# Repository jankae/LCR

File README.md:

# LCR Meter

### Key specifications
* Measurement frequency: 100Hz-200kHz
* Usable impedance range: 20mOhm-1MOhm (measurements above and below this range are possible but due to very low ADC values, the reported phase will be quite noisy)
### Some useful features
* Optionally apply DC bias voltage up to 10V (measure effective capacitance of MLCCs)
* Autoranging
* Open/Short calibration (lead compensation)
* Fully configurable sweep, showing up to two parameters across frequency:
  * Impedance
  * Phase
  * Capacitance
  * Inductance
  * ESR
  * Quality factor
##### Example of a sweep, showing the self-resonant frequency of a capacitor at approximately 5.5kHz

#### Modified version:
* Two possible toolchains: System Workbench for STM32 or IAR
* Slightly modified PCB
* Laser-cut acrylic case
##### Resistance measurement 1 kOhm +- 0.1%

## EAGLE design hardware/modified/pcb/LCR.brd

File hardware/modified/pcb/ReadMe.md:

Changed electrical circuit and printed circuit board:
- TAG-CONNECT ICSP connector replaced with pin header
- SI8651EB-B-IU replaced by ADuM1401CRWZ
- added USBLC6-2P6 for ESD protection on USB
- the display pin header is moved closer to the edge of the board for a display tighter fit
- added a fourth hole for mounting

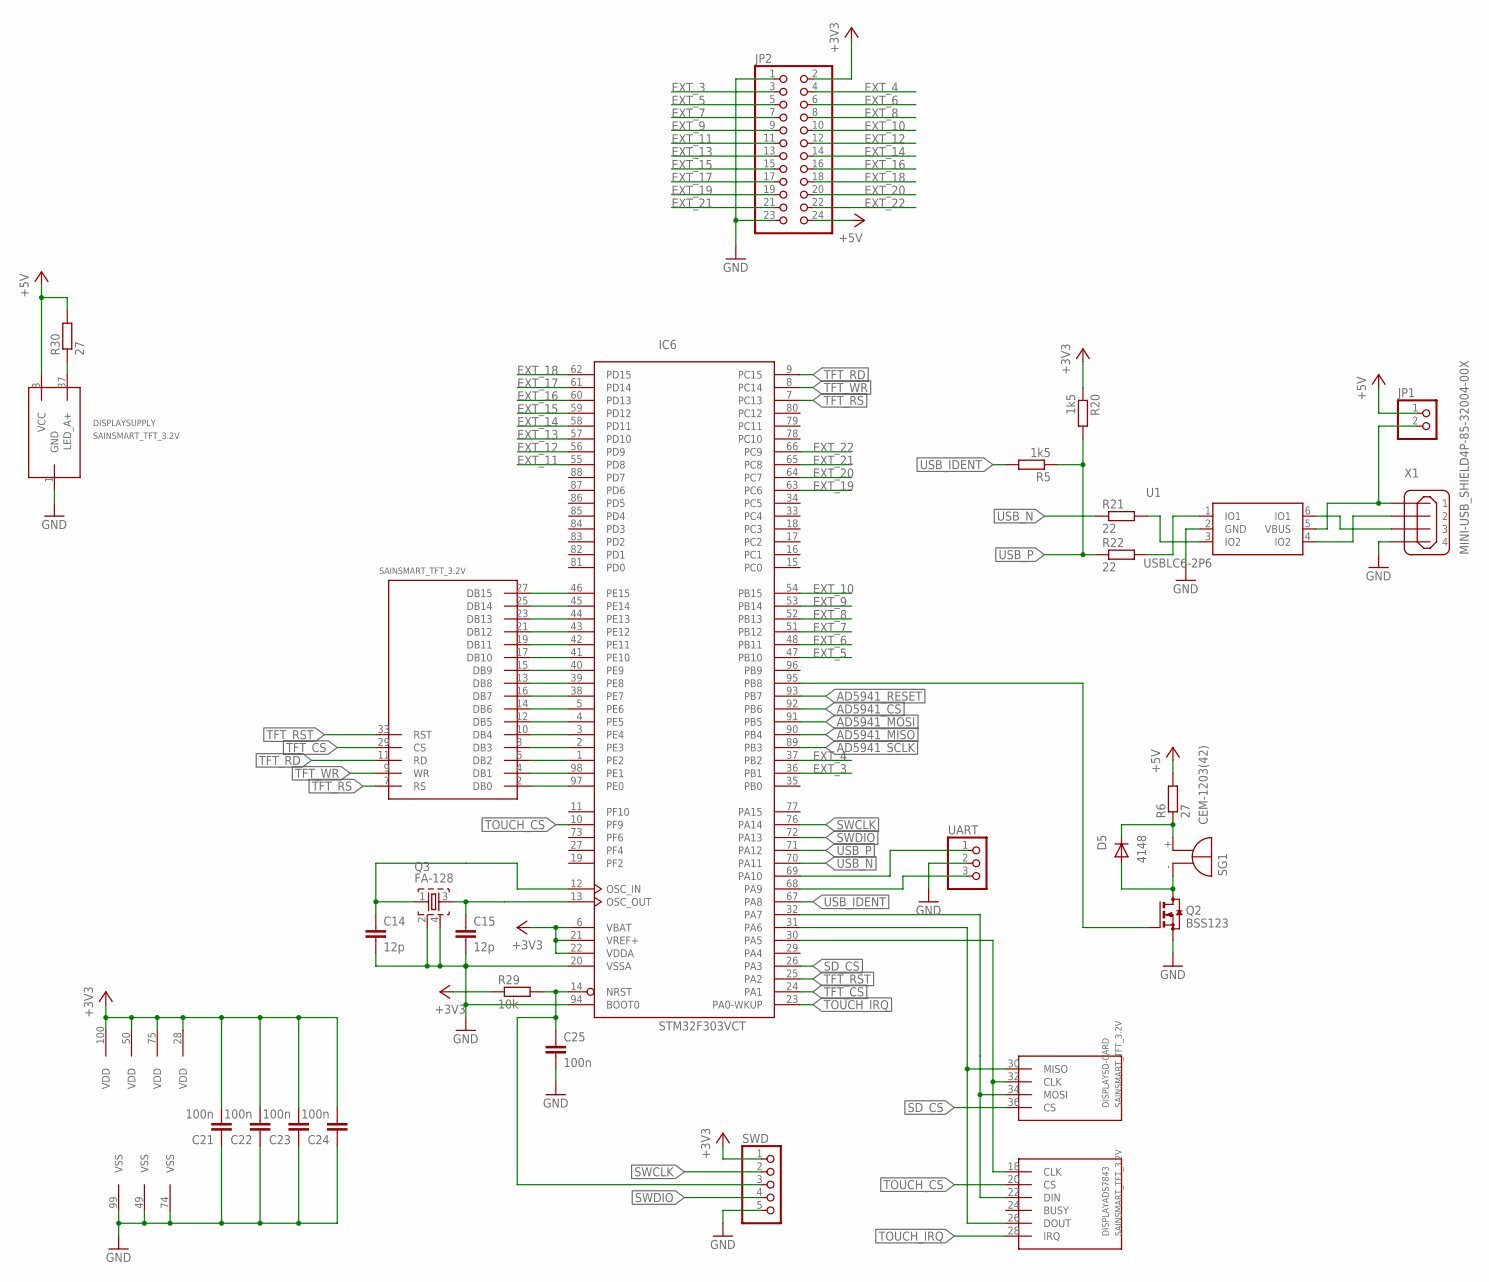
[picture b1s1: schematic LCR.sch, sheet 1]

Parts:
C14, C15: 12p; C0603K
C21, C22, C23, C24, C25: 100n; C0603K
D5: 4148; SOD123
DISPLAY: SAINSMART_TFT_3.2V; SAINSMART_ANGLED
IC6: STM32F303VCT; LQFP100
JP1: PINHD-1X2; 1X02
JP2: PINHD-2X12; 2X12
Q2: BSS123; SOT23
Q3: FA-128
R5, R20: 1k5; R0603
R6, R30: 27; R1206
R21, R22: 22; R0603
R29: 10k; R0603
SG1: CEM-1203(42); F/QMBIII
SWD: PINHD-1X5; 1X05
U1: USBLC6-2P6; SOT23-6
UART: PINHD-1X3; 1X03
X1: MINI-USB_SHIELD4P-85-32004-00X; 85-32004-00X

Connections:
+3V3: C21.2, C22.2, C23.2, C24.2, IC6.6 (VBAT), IC6.21 (VREF+), IC6.22 (VDDA), IC6.28 (VDD), IC6.50 (VDD), IC6.75 (VDD), IC6.100 (VDD), JP2.2, R20.1, R29.1, SWD.1; also elsewhere on the board
+5V: DISPLAY.3 (VCC), JP1.1, JP2.24, R6.2, R30.2; also elsewhere on the board
AD5941_CS: IC6.92 (PB6); also elsewhere on the board
AD5941_MISO: IC6.90 (PB4); also elsewhere on the board
AD5941_MOSI: IC6.91 (PB5); also elsewhere on the board
AD5941_RESET: IC6.93 (PB7)
AD5941_SCLK: IC6.89 (PB3); also elsewhere on the board
EXT_3: IC6.36 (PB1), JP2.3
EXT_4: IC6.37 (PB2), JP2.4
EXT_5: IC6.47 (PB10), JP2.5
EXT_6: IC6.48 (PB11), JP2.6
EXT_7: IC6.51 (PB12), JP2.7
EXT_8: IC6.52 (PB13), JP2.8
EXT_9: IC6.53 (PB14), JP2.9
EXT_10: IC6.54 (PB15), JP2.10
EXT_11: IC6.55 (PD8), JP2.11
EXT_12: IC6.56 (PD9), JP2.12
EXT_13: IC6.57 (PD10), JP2.13
EXT_14: IC6.58 (PD11), JP2.14
EXT_15: IC6.59 (PD12), JP2.15
EXT_16: IC6.60 (PD13), JP2.16
EXT_17: IC6.61 (PD14), JP2.17
EXT_18: IC6.62 (PD15), JP2.18
EXT_19: IC6.63 (PC6), JP2.19
EXT_20: IC6.64 (PC7), JP2.20
EXT_21: IC6.65 (PC8), JP2.21
EXT_22: IC6.66 (PC9), JP2.22
GND: C14.2, C15.2, C21.1, C22.1, C23.1, C24.1, C25.2, DISPLAY.1 (GND), IC6.20 (VSSA), IC6.49 (VSS), IC6.74 (VSS), IC6.94 (BOOT0), IC6.99 (VSS), JP2.1, JP2.23, Q2.2 (S), Q3.2, Q3.4, SWD.5, U1.2 (GND), UART.2, X1.4; also elsewhere on the board
unnamed: R21.2, U1.3 (IO2)
unnamed: IC6.95 (PB8), Q2.1 (G)
unnamed: R22.2, U1.1 (IO1)
unnamed: DISPLAY.2 (DB0), IC6.97 (PE0)
unnamed: DISPLAY.4 (DB1), IC6.98 (PE1)
unnamed: DISPLAY.6 (DB2), IC6.1 (PE2)
unnamed: DISPLAY.8 (DB3), IC6.2 (PE3)
unnamed: DISPLAY.22 (DIN), DISPLAY.34 (MOSI), IC6.32 (PA7)
unnamed: DISPLAY.10 (DB4), IC6.3 (PE4)
unnamed: DISPLAY.12 (DB5), IC6.4 (PE5)
unnamed: DISPLAY.14 (DB6), IC6.5 (PE6)
unnamed: DISPLAY.16 (DB7), IC6.38 (PE7)
unnamed: DISPLAY.26 (DOUT), DISPLAY.30 (MISO), IC6.31 (PA6)
unnamed: DISPLAY.18 (CLK), DISPLAY.32 (CLK), IC6.30 (PA5)
unnamed: C14.1, IC6.12 (OSC_IN), Q3.1
unnamed: C15.1, IC6.13 (OSC_OUT), Q3.3
unnamed: U1.6 (IO1), X1.3
unnamed: U1.4 (IO2), X1.2
unnamed: DISPLAY.37 (LED_A+), R30.1
unnamed: DISPLAY.13 (DB8), IC6.39 (PE8)
unnamed: DISPLAY.15 (DB9), IC6.40 (PE9)
unnamed: DISPLAY.17 (DB10), IC6.41 (PE10)
unnamed: DISPLAY.19 (DB11), IC6.42 (PE11)
unnamed: JP1.2, U1.5 (VBUS), X1.1
unnamed: D5.C, R6.1, SG1.+ (-)
unnamed: DISPLAY.21 (DB12), IC6.43 (PE12)
unnamed: DISPLAY.23 (DB13), IC6.44 (PE13)
unnamed: DISPLAY.25 (DB14), IC6.45 (PE14)
unnamed: DISPLAY.27 (DB15), IC6.46 (PE15)
unnamed: D5.A, Q2.3 (D), SG1.- (+)
NRST: C25.1, IC6.14 (NRST), R29.2, SWD.3
RX: IC6.69 (PA10), UART.1
SD_CS: DISPLAY.36 (CS), IC6.26 (PA3)
SWCLK: IC6.76 (PA14), SWD.2
SWDIO: IC6.72 (PA13), SWD.4
TFT_CS: DISPLAY.29 (CS), IC6.24 (PA1)
TFT_RD: DISPLAY.11 (RD), IC6.9 (PC15)
TFT_RS: DISPLAY.7 (RS), IC6.7 (PC13)
TFT_RST: DISPLAY.33 (RST), IC6.25 (PA2)
TFT_WR: DISPLAY.9 (WR), IC6.8 (PC14)
TOUCH_CS: DISPLAY.20 (CS), IC6.10 (PF9)
TOUCH_IRQ: DISPLAY.28 (IRQ), IC6.23 (PA0-WKUP)
TX: IC6.68 (PA9), UART.3
USB_IDENT: IC6.67 (PA8), R5.2
USB_N: IC6.70 (PA11), R21.1
USB_P: IC6.71 (PA12), R5.1, R20.2, R22.1

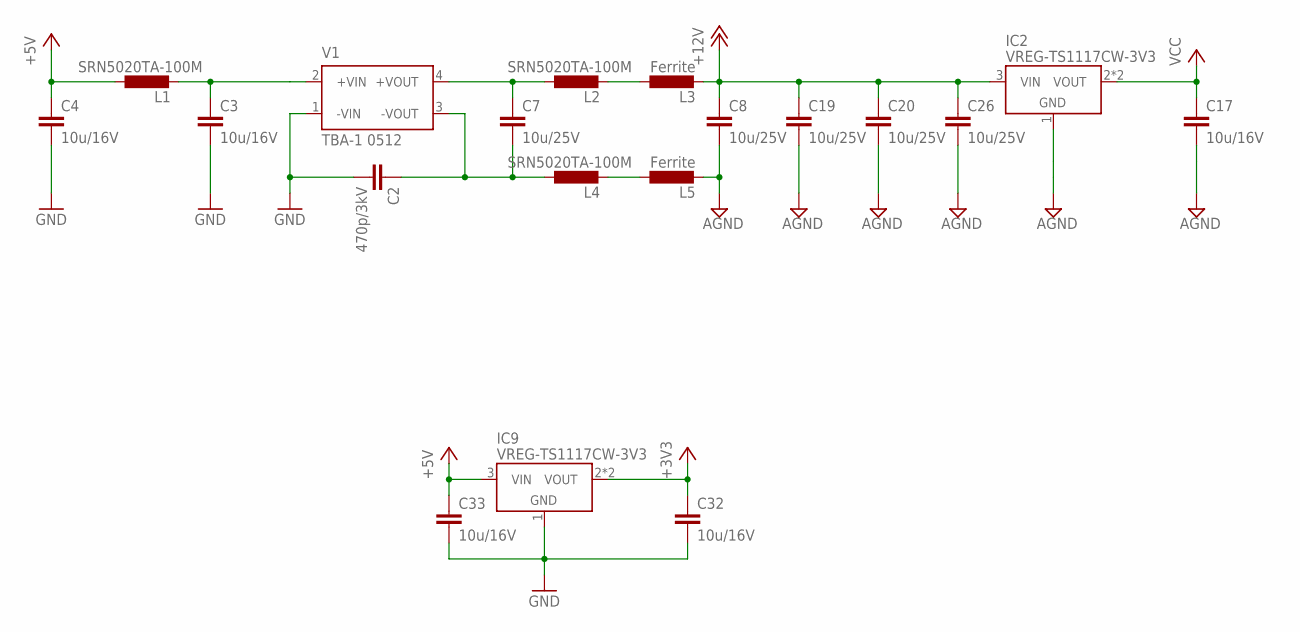
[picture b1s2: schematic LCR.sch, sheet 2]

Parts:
C2: 470p/3kV; C1812
C3, C4, C17, C32, C33: 10u/16V; C1206K
C7, C8, C19, C20, C26: 10u/25V; C1206K
IC2, IC9: VREG-TS1117CW-3V3; SOT223
L1, L2, L4: SRN5020TA-100M; SRN5040
L3, L5: Ferrite; R0603
V1: TBA-1 0512; TME

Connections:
+3V3: C32.1, IC9.2 (VOUT), IC9.4 (VOUT); also elsewhere on the board
+5V: C4.1, C33.1, IC9.3 (VIN), L1.P$1 (1); also elsewhere on the board
+12V: C8.1, C19.1, C20.1, C26.1, IC2.3 (VIN), L3.2; also elsewhere on the board
AGND: C8.2, C17.2, C19.2, C20.2, C26.2, IC2.1 (GND), L5.2; also elsewhere on the board
GND: C2.2, C3.2, C4.2, C32.2, C33.2, IC9.1 (GND), V1.1 (-VIN); also elsewhere on the board
unnamed: C3.1, L1.P$2 (2), V1.2 (+VIN)
unnamed: C7.1, L2.P$1 (1), V1.4 (+VOUT)
unnamed: C2.1, C7.2, L4.P$1 (1), V1.3 (-VOUT)
unnamed: L2.P$2 (2), L3.1
unnamed: L4.P$2 (2), L5.1
VCC: C17.1, IC2.2 (VOUT), IC2.4 (VOUT); also elsewhere on the board

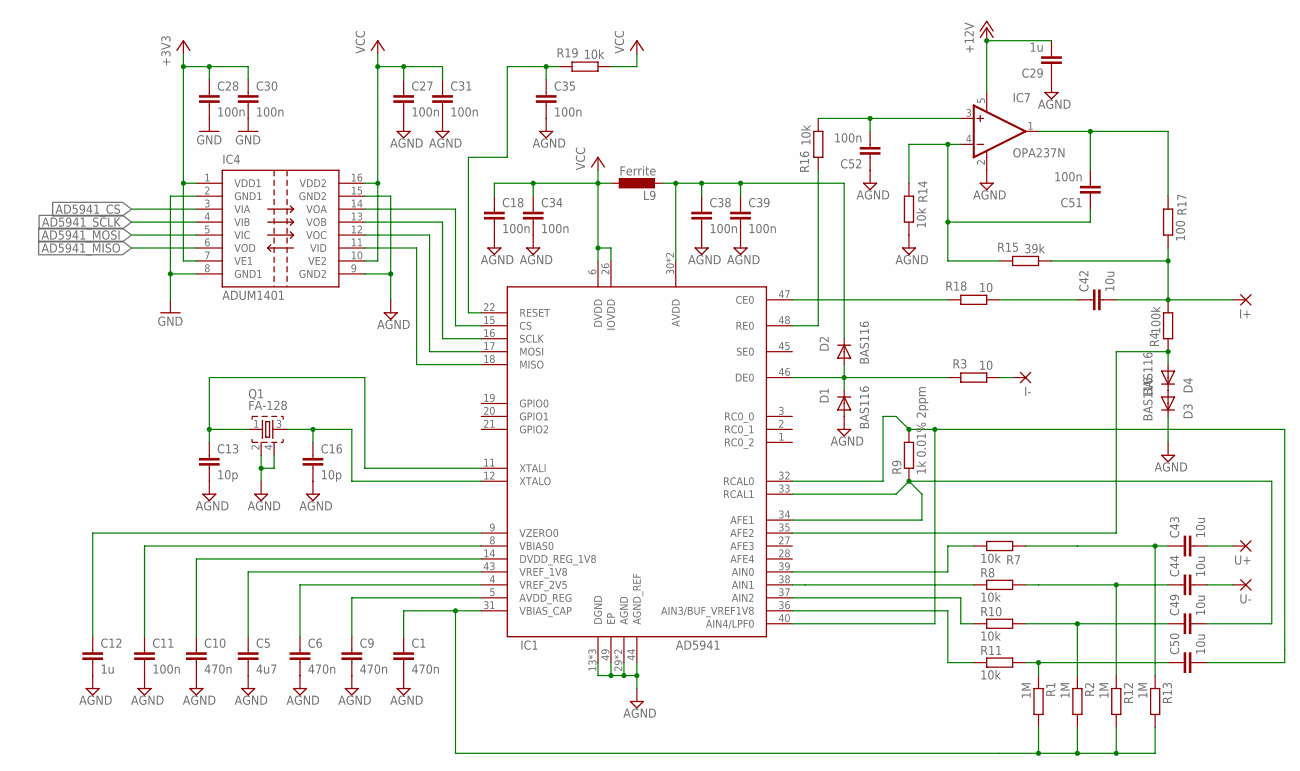
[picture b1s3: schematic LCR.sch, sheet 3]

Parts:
C1, C6, C9, C10: 470n; C0603K
C5: 4u7; C0603K
C11, C18, C27, C28, C30, C31, C34, C35, C38, C39, C51, C52: 100n; C0603K
C12, C29: 1u; C0603K
C13, C16: 10p; C0603K
C42, C43, C44, C49, C50: 10u; C1206K
D1, D2, D3, D4: BAS116; SOD123
I+: 2,54/1,1
I-: 2,54/1,1
IC1: AD5941; QFN50P700X700X80-49T510N
IC4: ADUM1401; SO16W
IC7: OPA237N; SOT23-5
L9: Ferrite; R0603
Q1: FA-128
R1, R2, R12, R13: 1M; R0603
R3, R18: 10; R0603
R4: 100k; R0603
R7, R8, R10, R11, R14, R16, R19: 10k; R0603
R9: 1k 0.01% 2ppm; M0805
R15: 39k; R0603
R17: 100; R0603
U+: 2,54/1,1
U-: 2,54/1,1

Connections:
+3V3: C28.1, C30.1, IC4.1 (VDD1), IC4.7 (VE1); also elsewhere on the board
+12V: C29.2, IC7.5 (V+); also elsewhere on the board
AD5941_CS: IC4.3 (VIA); also elsewhere on the board
AD5941_MISO: IC4.6 (VOD); also elsewhere on the board
AD5941_MOSI: IC4.5 (VIC); also elsewhere on the board
AD5941_SCLK: IC4.4 (VIB); also elsewhere on the board
AGND: C1.2, C5.2, C6.2, C9.2, C10.2, C11.2, C12.2, C13.2, C16.2, C18.2, C27.2, C29.1, C31.2, C34.2, C35.2, C38.2, C39.2, C52.1, D1.A, D3.C, IC1.13 (DGND), IC1.23 (DGND), IC1.25 (DGND), IC1.29 (AGND), IC1.42 (AGND), IC1.44 (AGND_REF), IC1.49 (EP), IC4.9 (GND2), IC4.15 (GND2), IC7.2 (V-), Q1.2, Q1.4, R14.1; also elsewhere on the board
GND: C28.2, C30.2, IC4.2 (GND1), IC4.8 (GND1); also elsewhere on the board
I+: C42.2, I+.1, R4.1, R15.1, R17.1
I-: I-.1, R3.1
unnamed: C1.1, IC1.31 (VBIAS_CAP), R1.2, R2.2, R12.2, R13.2
unnamed: C6.1, IC1.4 (VREF_2V5)
unnamed: C5.1, IC1.43 (VREF_1V8)
unnamed: C9.1, IC1.5 (AVDD_REG)
unnamed: C10.1, IC1.14 (DVDD_REG_1V8)
unnamed: C11.1, IC1.8 (VBIAS0)
unnamed: C12.1, IC1.9 (VZERO0)
unnamed: C16.1, IC1.12 (XTALO), Q1.3
unnamed: C13.1, IC1.11 (XTALI), Q1.1
unnamed: IC1.17 (MOSI), IC4.12 (VOC)
unnamed: C42.1, R18.1
unnamed: C35.1, IC1.22 (RESET), R19.2
unnamed: IC1.15 (CS), IC4.14 (VOA)
unnamed: IC1.16 (SCLK), IC4.13 (VOB)
unnamed: IC1.18 (MISO), IC4.11 (VID)
unnamed: C38.1, C39.1, D2.C, IC1.30 (AVDD), IC1.41 (AVDD), L9.2
unnamed: IC1.47 (CE0), R18.2
unnamed: IC1.39 (AIN0), R7.1
unnamed: IC1.38 (AIN1), R8.1
unnamed: C44.1, R8.2, R12.1
unnamed: C43.1, R7.2, R13.1
unnamed: C49.2, IC1.33 (RCAL1), IC1.34 (AFE1), R9.1
unnamed: IC1.37 (AIN2), R10.1
unnamed: IC1.36 (AIN3/BUF_VREF1V8), R11.1
unnamed: C50.1, R1.1, R11.2
unnamed: C49.1, R2.1, R10.2
unnamed: IC1.48 (RE0), R16.2
unnamed: C52.2, IC7.3 (+IN), R16.1
unnamed: C51.1, IC7.4 (-IN), R14.2, R15.2
unnamed: C51.2, IC7.1 (OUT), R17.2
unnamed: D1.C, D2.A, IC1.46 (DE0), R3.2
unnamed: D4.A, IC1.35 (AFE2), R4.2
unnamed: D3.A, D4.C
unnamed: C50.2, IC1.32 (RCAL0), IC1.40 (AIN4/LPF0), R9.2
U+: C43.2, U+.1
U-: C44.2, U-.1
VCC: C18.1, C27.1, C31.1, C34.1, IC1.6 (DVDD), IC1.26 (IOVDD), IC4.10 (VE2), IC4.16 (VDD2), L9.1, R19.1; also elsewhere on the board

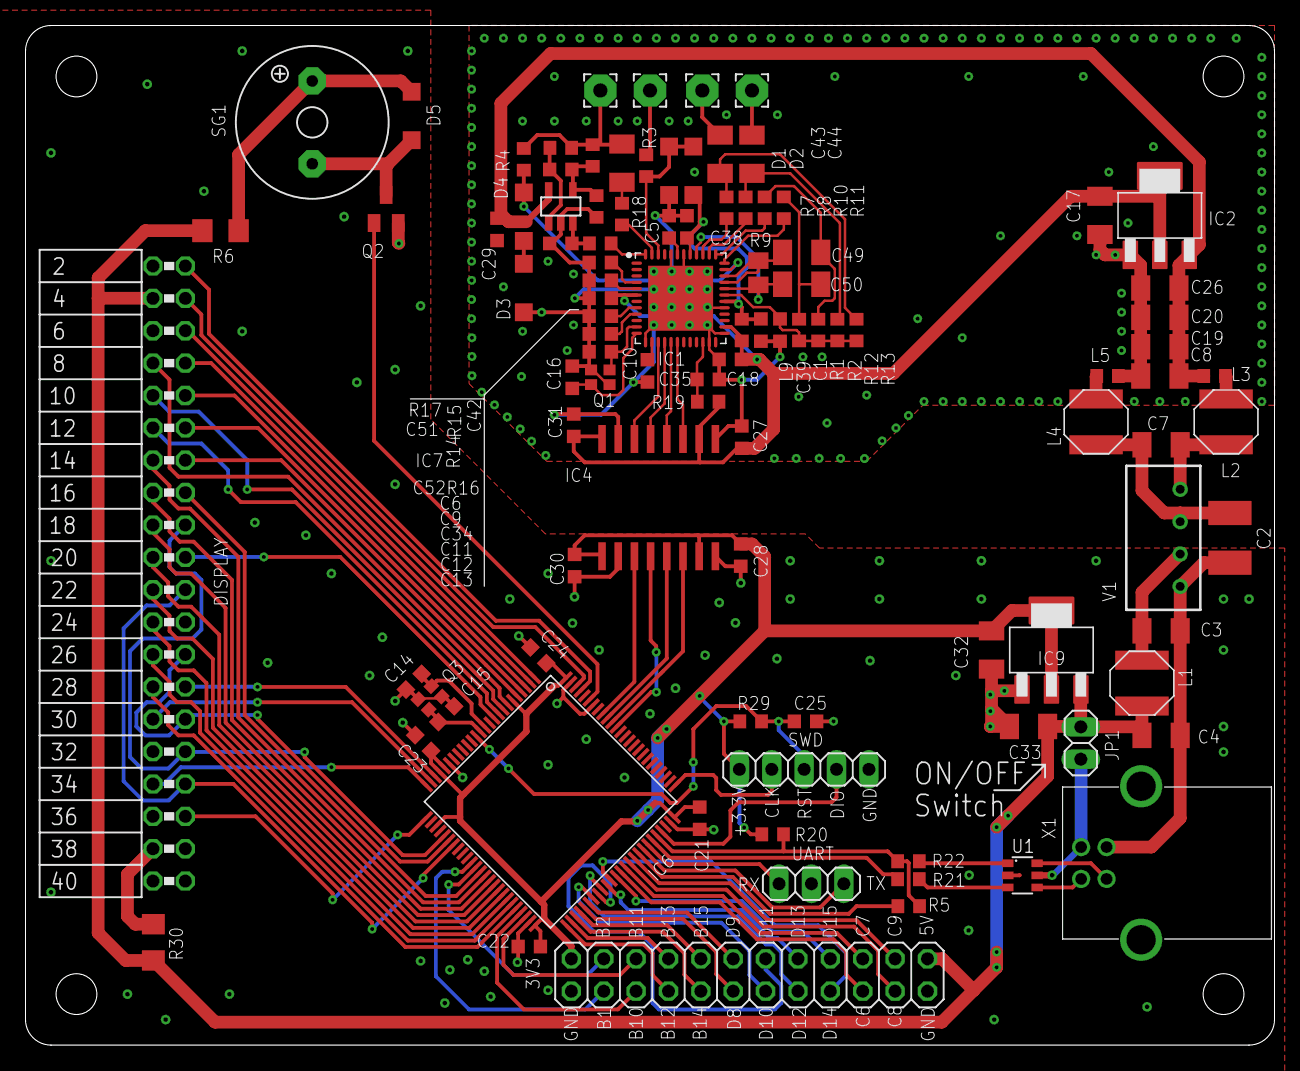
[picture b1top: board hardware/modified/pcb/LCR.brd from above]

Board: 2 copper layers, 98.0 x 80.0 mm, 101 parts (0 on the bottom side), 119 nets.

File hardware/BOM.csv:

Qty,Value,Device,Package,Parts,Mouser Link,
4,,"2,54/1,1","2,54/1,1","I+, I-, U+, U-",DNP,
1,,PINHD-1X2,1X02,JP1,available,
1,,PINHD-1X3,1X03,UART,available,
1,,PINHD-2X12,2X12,JP2,available,
1,,TC2030-MCP,TC2030-MCP,J1,DNP,
2,10,R-EU_R0603,R0603,"R3, R18",available,
1,100,R-EU_R0603,R0603,R17,available,
1,100k,R-EU_R0603,R0603,R4,available,
14,100n,C-EUC0603K,C0603K,"C11, C18, C21, C22, C23, C24, C25, C27, C28, C34, C38, C39, C51, C52",available,
7,10k,R-EU_R0603,R0603,"R7, R8, R10, R11, R14, R16, R29",available,
2,10p,C-EUC0603K,C0603K,"C13, C16",CC0603JRNPO9BN100,
5,10u,C-EUC1206K,C1206K,"C42, C43, C44, C49, C50",TMK316BJ106ML-T,
5,10u/16V,C-EUC1206K,C1206K,"C3, C4, C17, C32, C33",TMK316BJ106ML-T,
5,10u/25V,C-EUC1206K,C1206K,"C7, C8, C19, C20, C26",TMK316BJ106ML-T,
2,12p,C-EUC0603K,C0603K,"C14, C15",available,
4,1M,R-EU_R0603,R0603,"R1, R2, R12, R13",available,
1,1k 0.01% 2ppm,R-EU_M0805,M0805,R9,RG2012L-102-L-T05,
1,1k5,R-EU_R0603,R0603,R5,available,
2,1u,C-EUC0603K,C0603K,"C12, C29",available,
2,22,R-EU_R0603,R0603,"R21, R22",available,
2,27,R-EU_R1206,R1206,"R6, R30",available,
1,39k,R-EU_R0603,R0603,R15,available,
1,4148,DIODE-SOD123,SOD123,D5,MMSD4148T3G,
4,470n,C-EUC0603K,C0603K,"C1, C6, C9, C10",CC0603ZRY5V7BB474,
1,470p/3kV,C-EUC1812,C1812,C2,885352211001,
1,4u7,C-EUC0603K,C0603K,C5,EMK107ABJ475MA-T,
1,AD5941,AD5941,QFN50P700X700X80-49T510N,IC1,AD5941BCPZ-RL7,
4,BAS116,DIODE-SOD123,SOD123,"D1, D2, D3, D4",BAS116GWJ,
1,BSS123,BSS123,SOT23,Q2,available,
1,CEM-1203(42),F/QMBIII,F/QMBIII,SG1,CEM-1201(42),
2,FA-128,FA-128,FA-128,"Q1, Q3",FA-128 32.0000MF10Z-AJ5,FA-128 16.0000MF10Z-AC0
3,Ferrite,INDUCTOR0603,R0603,"L3, L5, L9",available,
1,MINI-USB_SHIELD4P-85-32004-00X,MINI-USB_SHIELD4P-85-32004-00X,85-32004-00X,X1,SS-52300-001,
1,OPA237N,OPA237N,SOT23-5,IC7,OPA237NA/3K,
1,SAINSMART_TFT_3.2V,SAINSMART_TFT_3.2V,SAINSMART_ANGLED,DISPLAY,available,
1,SI8651EB-B-IU,SI8651EB-B-IU,SOP63P600X175-16N,IC3,SI8651EB-B-IU,
3,SRN5020TA-100M,SRN5040,SRN5040,"L1, L2, L4",SRN5020TA-150M,
1,STM32F303VCT,STM32F303VCT,LQFP100,IC6,STM32F303VET6,
1,TBA-1 0512,TME0505S,TME,V1,TBA 1-0512,
2,VREG-TS1117CW-3V3,VREG-TS1117CW-3V3,SOT223,"IC2, IC9",TS1117BCW33 RPG,

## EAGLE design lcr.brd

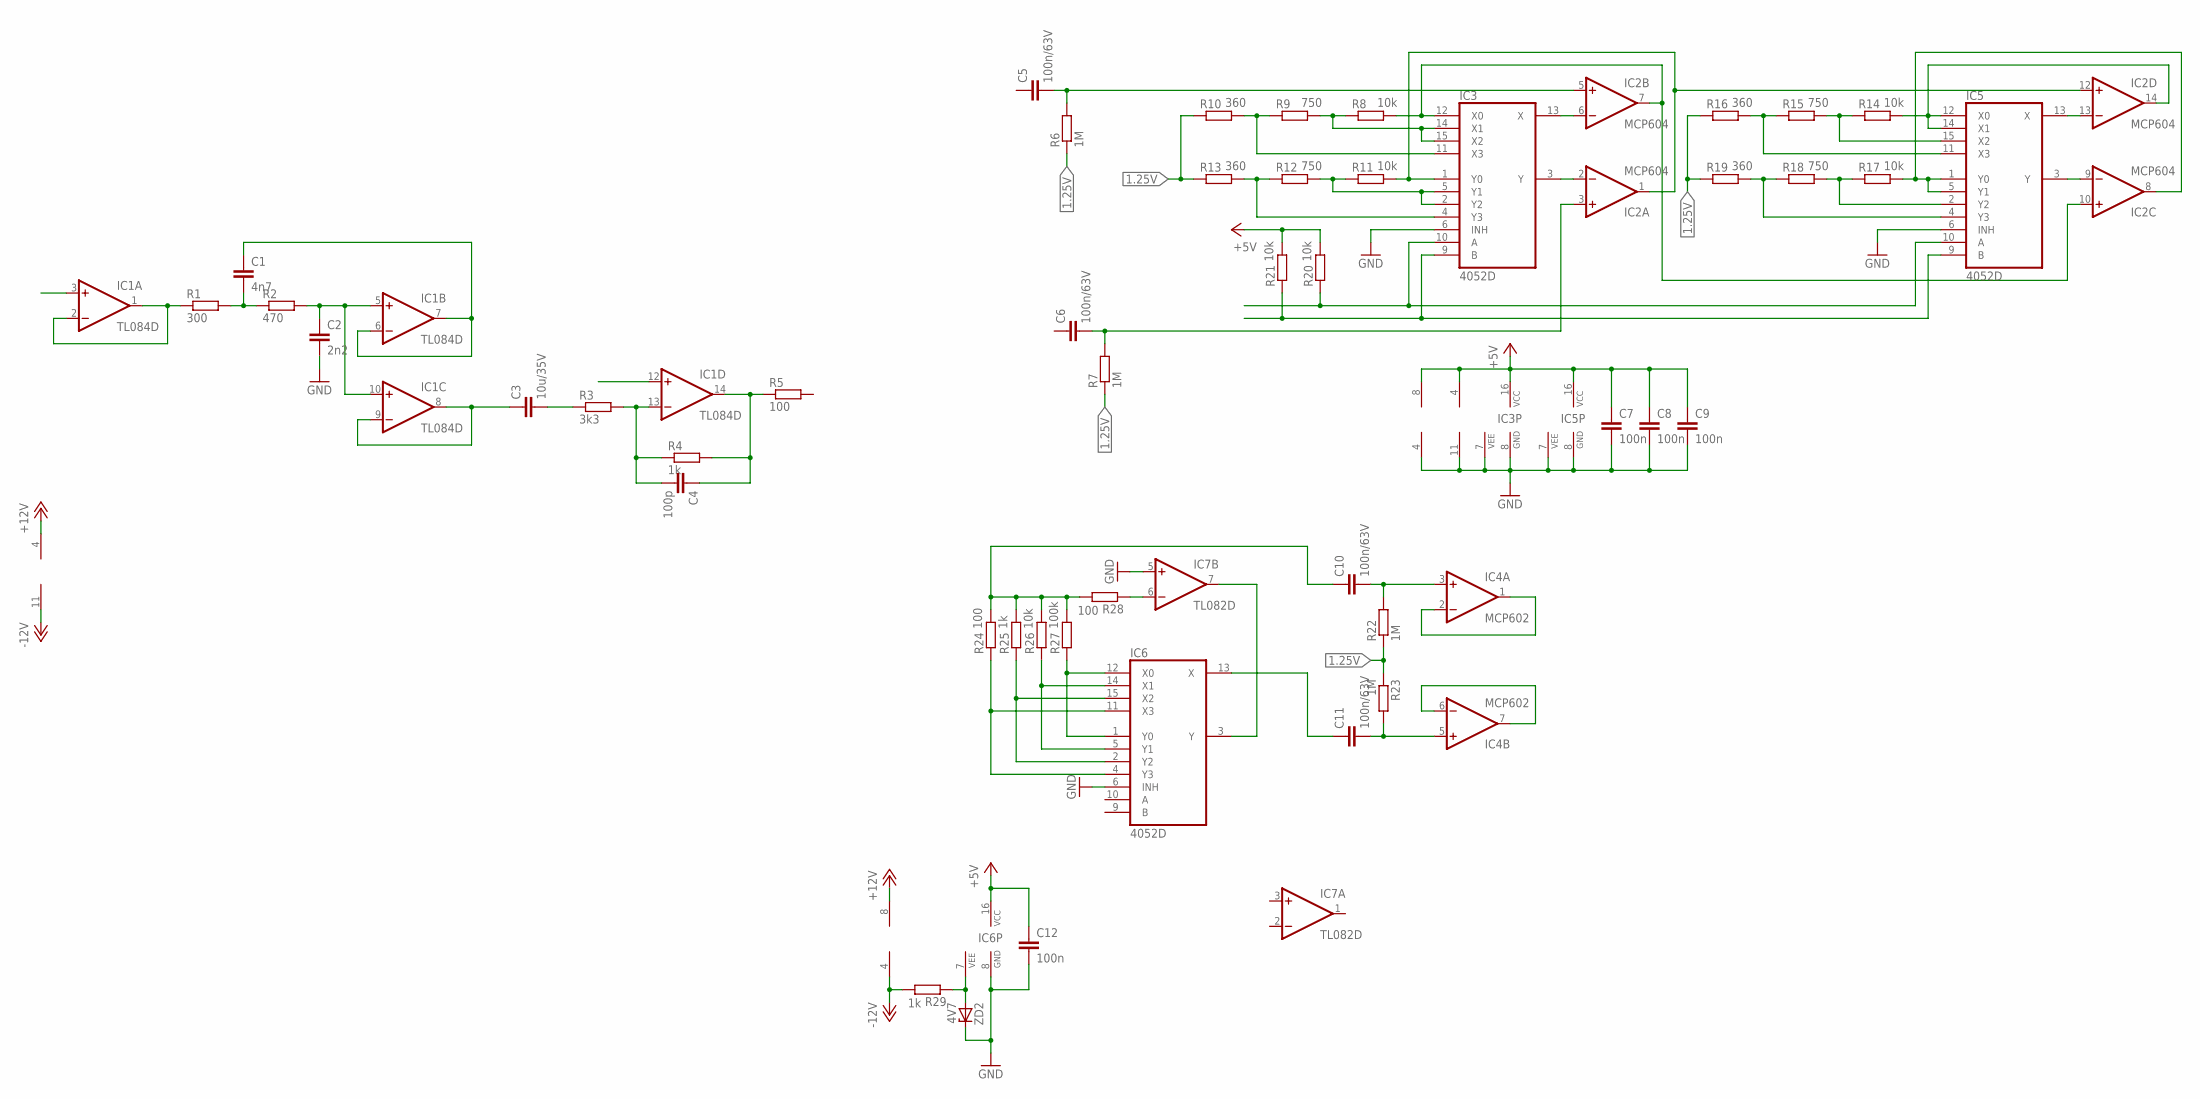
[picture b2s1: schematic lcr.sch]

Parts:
C1: 4n7; C0603K
C2: 2n2; C0603K
C3: 10u/35V; C1206K
C4: 100p; C0603K
C5, C6, C10, C11: 100n/63V; C1206K
C7, C8, C9, C12: 100n; C0603K
IC1: TL084D; SO14
IC2: MCP604; SO14
IC3, IC5, IC6: 4052D; SO16
IC4: MCP602; SO08
IC7: TL082D; SO08
R1: 300; R0603
R2: 470; R0603
R3: 3k3; R0603
R4, R25, R29: 1k; R0603
R5, R24, R28: 100; R0603
R6, R7, R22, R23: 1M; R0603
R8, R11, R14, R17, R20, R21, R26: 10k; R0603
R9, R12, R15, R18: 750; R0603
R10, R13, R16, R19: 360; R0603
R27: 100k; R0603
ZD2: 4V7; SOT23

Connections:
1.25V: R6.1, R7.1, R10.1, R13.1, R16.1, R19.1, R22.1, R23.1
+5V: C7.1, C8.1, C9.1, C12.1, IC2.4 (V+), IC3.16 (VCC), IC4.8 (V+), IC5.16 (VCC), IC6.16 (VCC), R20.2, R21.2
+12V: IC1.4 (V+), IC7.8 (V+)
-12V: IC1.11 (V-), IC7.4 (V-), R29.2
GND: C2.2, C7.2, C8.2, C9.2, C12.2, IC2.11 (V-), IC3.6 (INH), IC3.7 (VEE), IC3.8 (GND), IC4.4 (V-), IC5.6 (INH), IC5.7 (VEE), IC5.8 (GND), IC6.6 (INH), IC6.8 (GND), IC7.5 (+IN), ZD2.3 (C)
unnamed: IC1.1 (OUT), IC1.2 (-IN), R1.1
unnamed: C1.2, R1.2, R2.1
unnamed: C2.1, IC1.5 (+IN), IC1.10 (+IN), R2.2
unnamed: C1.1, IC1.6 (-IN), IC1.7 (OUT)
unnamed: C5.2, IC2.5 (+IN), R6.2
unnamed: C3.1, IC1.8 (OUT), IC1.9 (-IN)
unnamed: C3.2, R3.1
unnamed: C4.2, IC1.13 (-IN), R3.2, R4.1
unnamed: C4.1, IC1.14 (OUT), R4.2, R5.1
unnamed: C6.2, IC2.3 (+IN), R7.2
unnamed: IC3.4 (Y3), R12.1, R13.2
unnamed: IC3.11 (X3), R9.1, R10.2
unnamed: IC2.7 (OUT), IC2.10 (+IN), IC3.12 (X0), R8.2
unnamed: IC3.2 (Y2), IC3.5 (Y1), R11.1, R12.2
unnamed: IC3.14 (X1), IC3.15 (X2), R8.1, R9.2
unnamed: IC2.1 (OUT), IC2.12 (+IN), IC3.1 (Y0), R11.2
unnamed: IC2.6 (-IN), IC3.13 (X)
unnamed: IC2.9 (-IN), IC5.3 (Y)
unnamed: IC3.9 (B), IC5.9 (B), R21.1
unnamed: IC2.2 (-IN), IC3.3 (Y)
unnamed: IC2.14 (OUT), IC5.12 (X0), IC5.14 (X1), R14.2
unnamed: IC5.4 (Y3), R18.1, R19.2
unnamed: IC5.11 (X3), R15.1, R16.2
unnamed: IC5.2 (Y2), R17.1, R18.2
unnamed: C10.2, IC4.3 (+IN), R22.2
unnamed: IC2.8 (OUT), IC5.1 (Y0), IC5.5 (Y1), R17.2
unnamed: IC3.10 (A), IC5.10 (A), R20.1
unnamed: IC5.15 (X2), R14.1, R15.2
unnamed: IC2.13 (-IN), IC5.13 (X)
unnamed: C11.2, IC4.5 (+IN), R23.2
unnamed: IC4.6 (-IN), IC4.7 (OUT)
unnamed: IC4.1 (OUT), IC4.2 (-IN)
unnamed: IC6.3 (Y), IC7.7 (OUT)
unnamed: IC7.6 (-IN), R28.1
unnamed: C10.1, R24.2, R25.2, R26.2, R27.2, R28.2
unnamed: IC6.1 (Y0), IC6.12 (X0), R27.1
unnamed: IC6.5 (Y1), IC6.14 (X1), R26.1
unnamed: IC6.2 (Y2), IC6.15 (X2), R25.1
unnamed: IC6.4 (Y3), IC6.11 (X3), R24.1
unnamed: C11.1, IC6.13 (X)
unnamed: IC6.7 (VEE), R29.1, ZD2.1 (A)

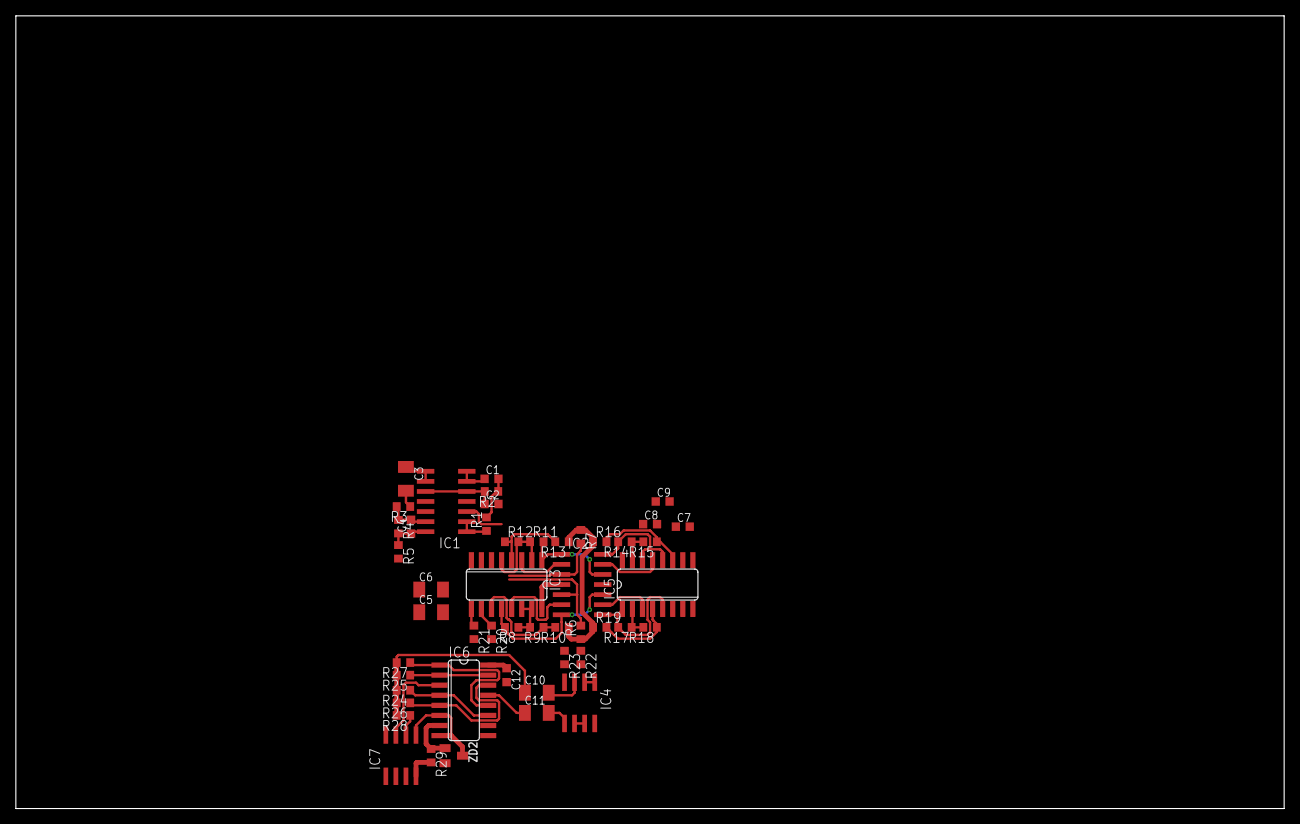
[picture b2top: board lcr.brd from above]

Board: 2 copper layers, 160.0 x 100.0 mm, 49 parts (0 on the bottom side), 46 nets.

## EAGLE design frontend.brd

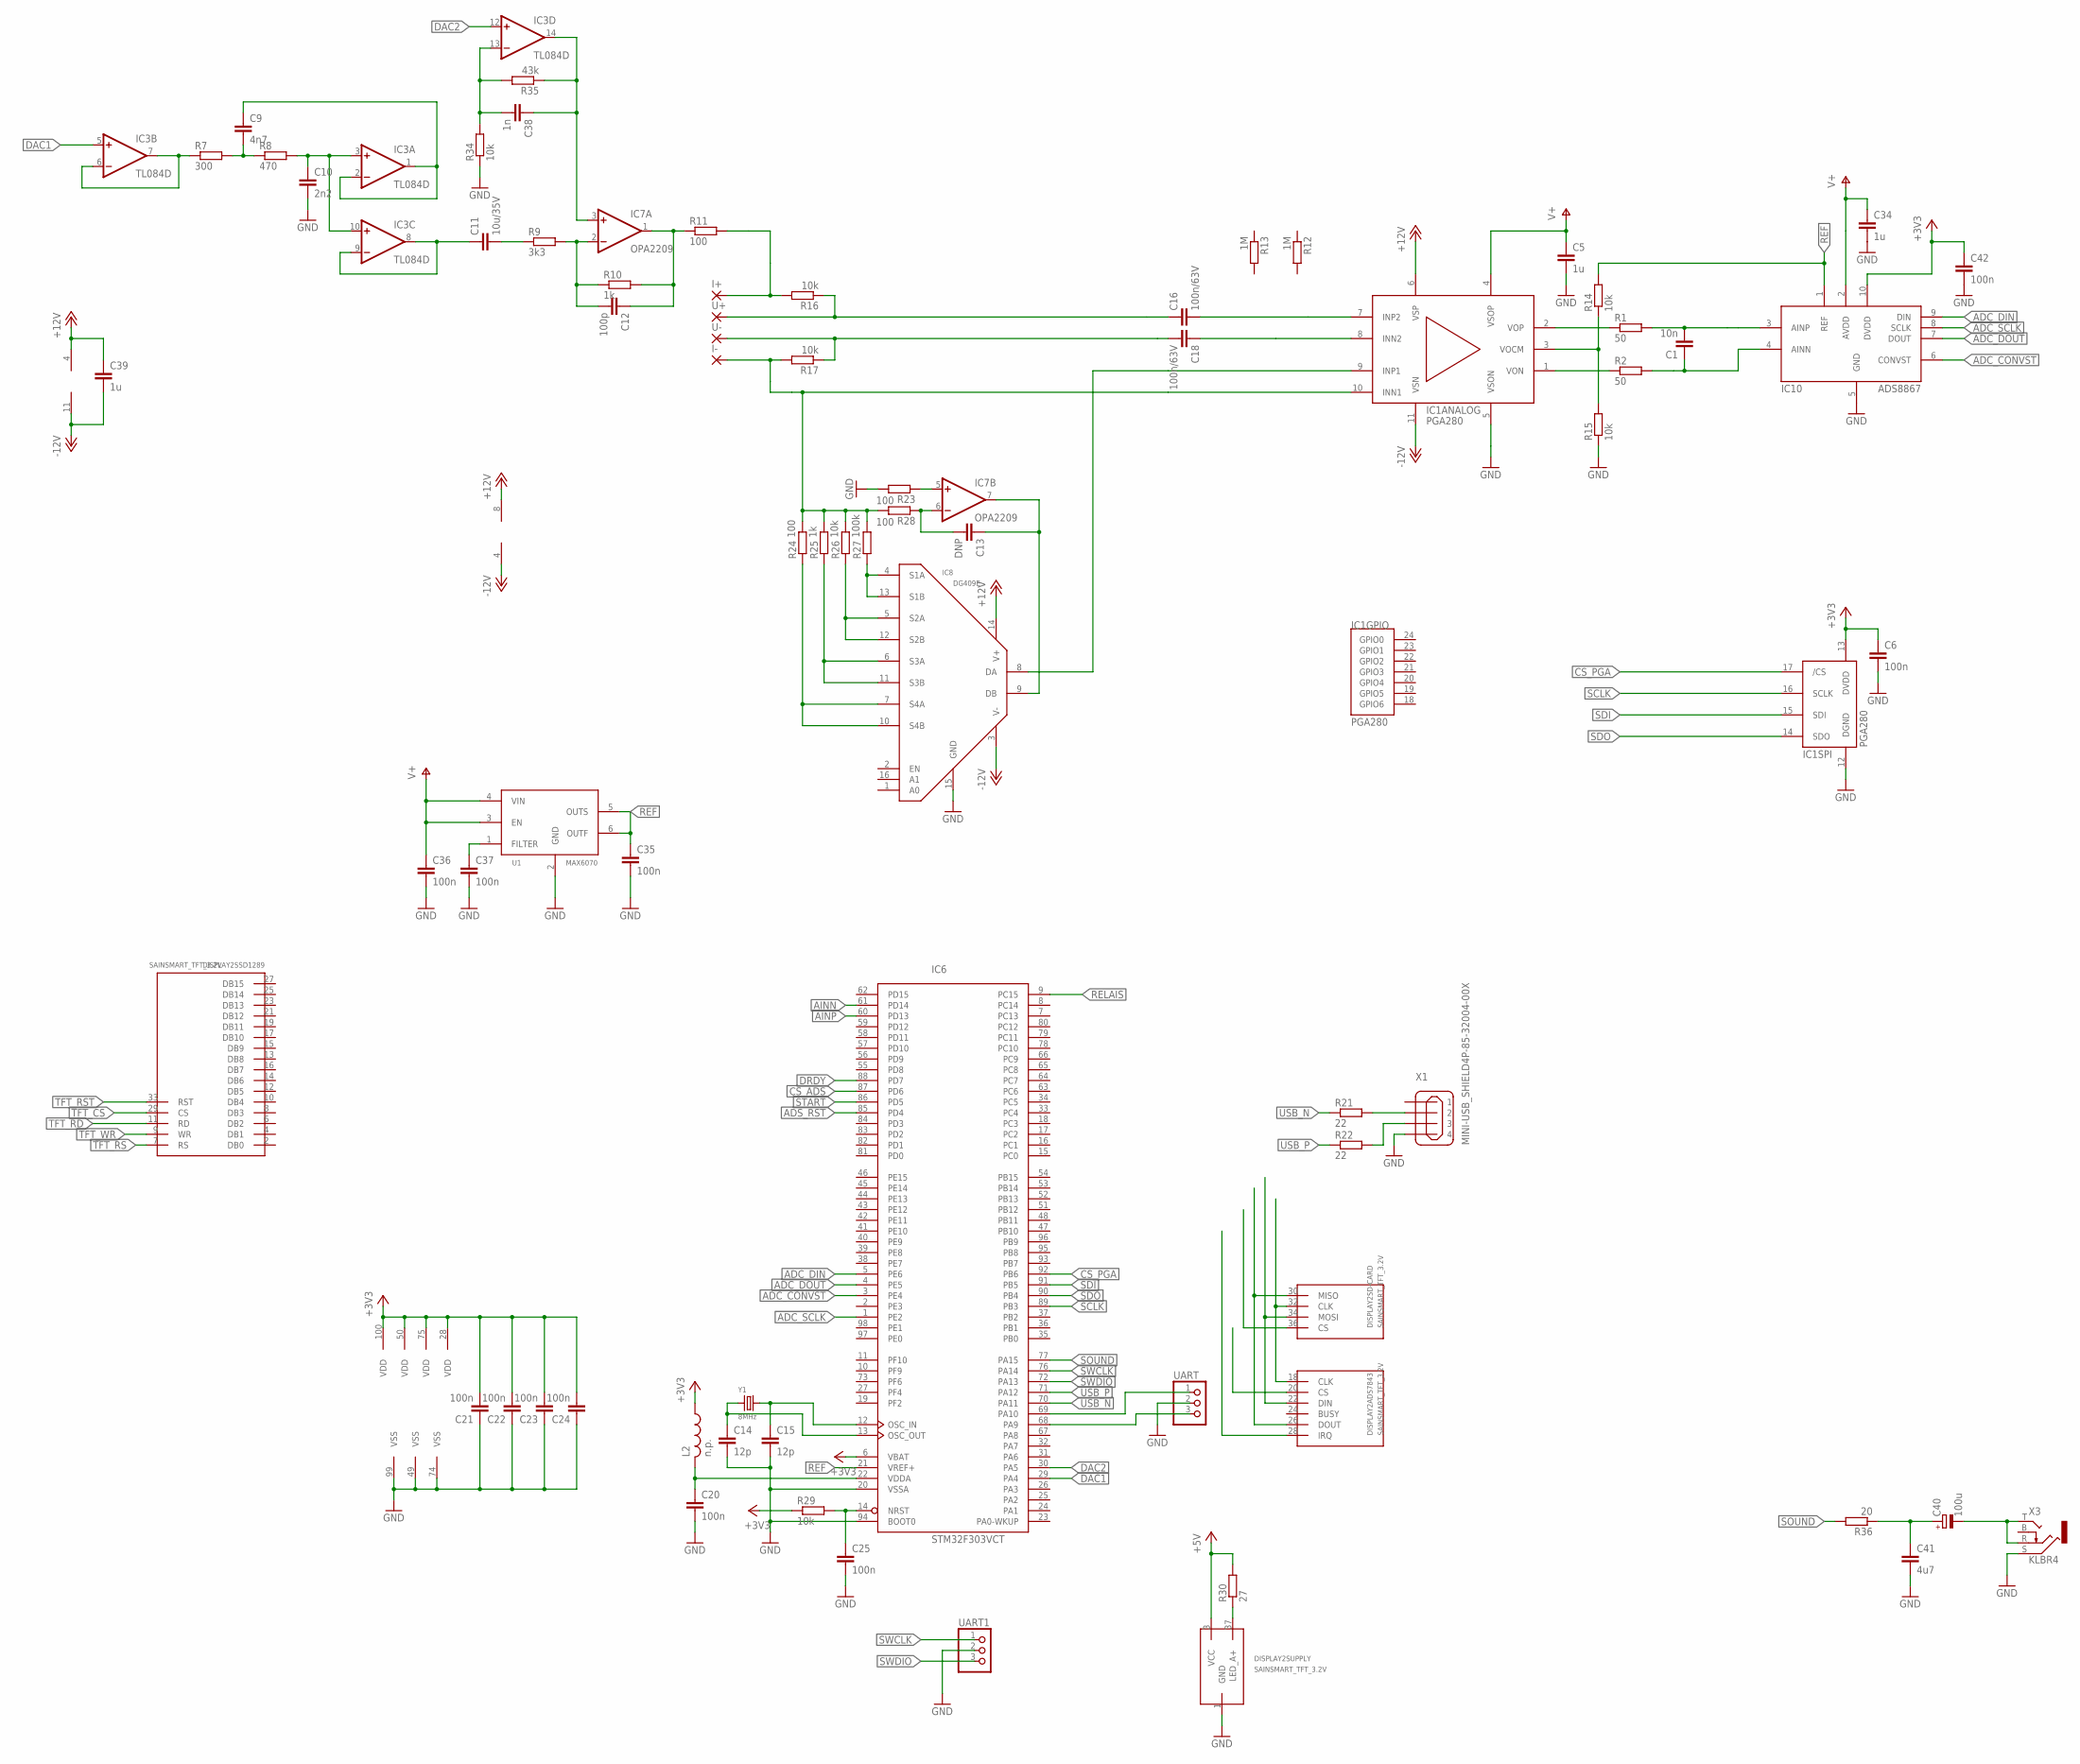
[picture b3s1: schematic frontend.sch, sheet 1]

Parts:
C1: 10n; C0603K
C5, C34, C39: 1u; C0603K
C6, C20, C21, C22, C23, C24, C25, C35, C36, C37, C42: 100n; C0603K
C9: 4n7; C0603K
C10: 2n2; C0603K
C11: 10u/35V; C1206K
C12: 100p; C0603K
C13: DNP; C0603K
C14, C15: 12p; C0603K
C16, C18: 100n/63V; C1206K
C38: 1n; C0603K
C40: 100u; E2,5-5
C41: 4u7; C1206K
DISPLAY2: SAINSMART_TFT_3.2V; SAINSMART_ANGLED
I+: SMD5; SMD2,54-5,08
I-: SMD5; SMD2,54-5,08
IC1: PGA280; TSSOP24
IC3: TL084D; SO14
IC6: STM32F303VCT; LQFP100
IC7: OPA2209; SO08
IC8: DG409E; TSSOP16
IC10: ADS8867; SOP50P490X110-10N
L2: n.p.; R0603
R1, R2: 50; R0603
R7: 300; R0603
R8: 470; R0603
R9: 3k3; R0603
R10, R25: 1k; R0603
R11, R23, R24, R28: 100; R0603
R12, R13: 1M; R0603
R14, R15, R16, R17, R26, R29, R34: 10k; R0603
R21, R22: 22; R0603
R27: 100k; R0603
R30: 27; R1206
R35: 43k; R0603
R36: 20; R1206
U1: MAX6070; SOT23-6L
U+: SMD5; SMD2,54-5,08
U-: SMD5; SMD2,54-5,08
UART, UART1: PINHD-1X3; 1X03
X1: MINI-USB_SHIELD4P-85-32004-00X; 85-32004-00X
X3: KLBR4
Y1: 8MHz; 3.2X2.5MM

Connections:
+3V3: C6.1, C21.2, C22.2, C23.2, C24.2, C42.1, IC1.13 (DVDD), IC6.6 (VBAT), IC6.28 (VDD), IC6.50 (VDD), IC6.75 (VDD), IC6.100 (VDD), IC10.10 (DVDD), L2.1, R29.1; also elsewhere on the board
+5V: DISPLAY2.3 (VCC), R30.2; also elsewhere on the board
+12V: C39.1, IC1.6 (VSP), IC3.4 (V+), IC7.8 (V+), IC8.14 (V+); also elsewhere on the board
-12V: C39.2, IC1.11 (VSN), IC3.11 (V-), IC7.4 (V-), IC8.3 (V-); also elsewhere on the board
ADC_CONVST: IC6.3 (PE4), IC10.6 (CONVST)
ADC_DIN: IC6.5 (PE6), IC10.9 (DIN)
ADC_DOUT: IC6.4 (PE5), IC10.7 (DOUT)
ADC_SCLK: IC6.1 (PE2), IC10.8 (SCLK)
ADS_RST: IC6.85 (PD4)
AINN: C1.1, IC6.61 (PD14), IC10.4 (AINN), R2.2
AINP: C1.2, IC6.60 (PD13), IC10.3 (AINP), R1.2
CS_ADS: IC6.87 (PD6)
CS_PGA: IC1.17 (/CS), IC6.92 (PB6)
DAC1: IC3.5 (+IN), IC6.29 (PA4)
DAC2: IC3.12 (+IN), IC6.30 (PA5)
DRDY: IC6.88 (PD7)
EXT4: C20.1, IC6.22 (VDDA), L2.2
GND: C5.2, C6.2, C10.2, C14.2, C15.2, C20.2, C21.1, C22.1, C23.1, C24.1, C25.2, C34.2, C35.2, C36.2, C37.2, C41.2, C42.2, DISPLAY2.1 (GND), IC1.5 (VSON), IC1.12 (DGND), IC6.20 (VSSA), IC6.49 (VSS), IC6.74 (VSS), IC6.94 (BOOT0), IC6.99 (VSS), IC8.15 (GND), IC10.5 (GND), R15.1, R23.2, R34.1, U1.2 (GND), UART.2, UART1.2, X1.4, X3.S; also elsewhere on the board
I+: I+.1, R11.2, R16.2
I-: I-.1, IC1.10 (INN1), R17.2, R24.2, R25.2, R26.2, R27.2, R28.2
unnamed: IC3.6 (-IN), IC3.7 (OUT), R7.1
unnamed: C9.2, R7.2, R8.1
unnamed: C10.1, IC3.3 (+IN), IC3.10 (+IN), R8.2
unnamed: C9.1, IC3.1 (OUT), IC3.2 (-IN)
unnamed: C16.2, IC1.7 (INP2)
unnamed: C11.1, IC3.8 (OUT), IC3.9 (-IN)
unnamed: C11.2, R9.1
unnamed: C12.2, IC7.2 (-IN), R9.2, R10.1
unnamed: C12.1, IC7.1 (OUT), R10.2, R11.1
unnamed: IC1.3 (VOCM), R14.1, R15.2
unnamed: C18.1, IC1.8 (INN2)
unnamed: C38.1, IC3.14 (OUT), IC7.3 (+IN), R35.1
unnamed: C38.2, IC3.13 (-IN), R34.2, R35.2
unnamed: IC1.9 (INP1), IC8.8 (DA)
unnamed: C13.1, IC7.7 (OUT), IC8.9 (DB)
unnamed: C40.+, C41.1, R36.1
unnamed: C37.1, U1.1 (FILTER)
unnamed: C13.2, IC7.6 (-IN), R28.1
unnamed: IC8.4 (S1A), IC8.13 (S1B), R27.1
unnamed: IC8.5 (S2A), IC8.12 (S2B), R26.1
unnamed: IC8.6 (S3A), IC8.11 (S3B), R25.1
unnamed: IC8.7 (S4A), IC8.10 (S4B), R24.1
unnamed: C40.-, X3.R, X3.T
unnamed: C15.1, IC6.12 (OSC_IN), Y1.3 (2)
unnamed: C14.1, IC6.13 (OSC_OUT), Y1.1
unnamed: R21.2, X1.2
unnamed: R22.2, X1.3
unnamed: DISPLAY2.22 (DIN), DISPLAY2.34 (MOSI)
unnamed: DISPLAY2.26 (DOUT), DISPLAY2.30 (MISO)
unnamed: DISPLAY2.18 (CLK), DISPLAY2.32 (CLK)
unnamed: C25.1, IC6.14 (NRST), R29.2
unnamed: DISPLAY2.37 (LED_A+), R30.1
unnamed: IC7.5 (+IN), R23.1
REF: C35.1, IC6.21 (VREF+), IC10.1 (REF), R14.2, U1.5 (OUTS), U1.6 (OUTF)
RELAIS: IC6.9 (PC15)
RX: IC6.69 (PA10), UART.1
SCLK: IC1.16 (SCLK), IC6.89 (PB3)
SDI: IC1.15 (SDI), IC6.91 (PB5)
SDO: IC1.14 (SDO), IC6.90 (PB4)
SOUND: IC6.77 (PA15), R36.2
START: IC6.86 (PD5)
SWCLK: IC6.76 (PA14), UART1.1
SWDIO: IC6.72 (PA13), UART1.3
TFT_CS: DISPLAY2.29 (CS)
TFT_RD: DISPLAY2.11 (RD)
TFT_RS: DISPLAY2.7 (RS)
TFT_RST: DISPLAY2.33 (RST)
TFT_WR: DISPLAY2.9 (WR)
TX: IC6.68 (PA9), UART.3
U+: C16.1, R16.1, U+.1
U-: C18.2, R17.1, U-.1
USB_N: IC6.70 (PA11), R21.1
USB_P: IC6.71 (PA12), R22.1
V+: C5.1, C34.1, C36.1, IC1.4 (VSOP), IC10.2 (AVDD), U1.3 (EN), U1.4 (VIN); also elsewhere on the board
VON: IC1.1 (VON), R2.1
VOP: IC1.2 (VOP), R1.1

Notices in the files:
parts and their libraries:
xmaker: Licensing: CC v3.0 Attribution-Share Alike
http://creativecommons.org/licenses/by-sa/3.0
tag-connect: ©2009 ROFA.cz - modified and updated by Robert Darlington ‹rdarlington@gmail.com›
